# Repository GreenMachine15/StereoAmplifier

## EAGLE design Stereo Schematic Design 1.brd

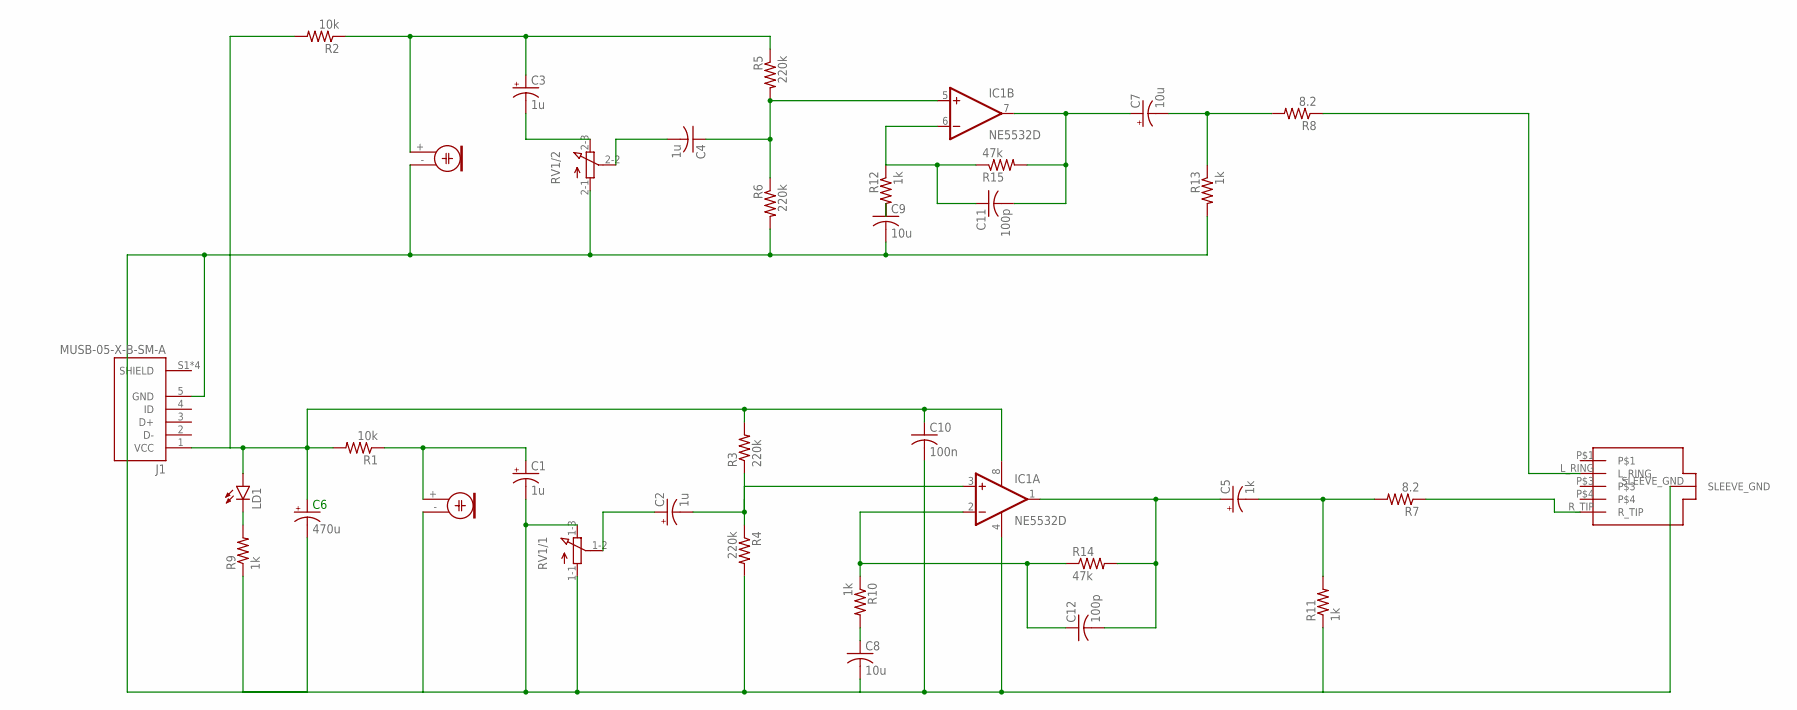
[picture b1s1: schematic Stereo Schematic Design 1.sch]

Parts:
C1, C2, C3: 1u; E3,5-8
C4: 1u; C0603
C5: 1k; E3,5-8
C6: 470u; E3,5-8
C7: 10u; E3,5-8
C8, C9: 10u; C0805
C10: 100n; C1206
C11, C12: 100p; C0603
IC1: NE5532D; SO08
J1: MUSB-05-X-B-SM-A; SAMTEC_MUSB-05-X-B-SM-A
LD1: LED3MM
M1, M2: ELECTRET_MICROPHON-TOM-1545P-R; TOM-1545P-R
R1, R2: 10k; R0805
R3, R4, R5, R6: 220k; R0603
R7, R8: 8.2; R0805
R9, R10, R11, R12: 1k; R1206
R13: 1k; 0204/7
R14, R15: 47k; 0204/7
RV1: 3RP/1610G
U$1: KORTAKJACK; REDPHONEJACK

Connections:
unnamed: C6.+, C10.1, IC1.8 (V+), J1.1 (VCC), LD1.A, R1.2, R2.2, R3.2
unnamed: LD1.K (C), R9.2
unnamed: C1.-, C8.2, C9.2, C10.2, IC1.4 (V-), J1.5 (GND), M2.- (2), R4.2, R6.2, R11.1, R13.2, RV1.1-1 (A), RV1.1-3 (E), RV1.2-1 (A), U$1.SLEEVE_GND
unnamed: C1.+, M1.+ (1), R1.1
unnamed: C8.1, R10.2
unnamed: C2.+, RV1.1-2 (S)
unnamed: C12.1, IC1.2 (-IN), R10.1, R14.1
unnamed: C5.+, C12.2, IC1.1 (OUT), R14.2
unnamed: C6.-, R9.1
unnamed: C2.-, IC1.3 (+IN), R3.1, R4.1
unnamed: C5.-, R7.2, R11.2
unnamed: R7.1, U$1.R_TIP
unnamed: C3.+, M2.+ (1), R2.1, R5.1
unnamed: C3.-, RV1.2-3 (E)
unnamed: C4.2, RV1.2-2 (S)
unnamed: C4.1, IC1.5 (+IN), R5.2, R6.1
unnamed: C11.1, IC1.6 (-IN), R12.1, R15.1
unnamed: C9.1, R12.2
unnamed: C7.+, C11.2, IC1.7 (OUT), R15.2
unnamed: C7.-, R8.2, R13.1
unnamed: R8.1, U$1.L_RING

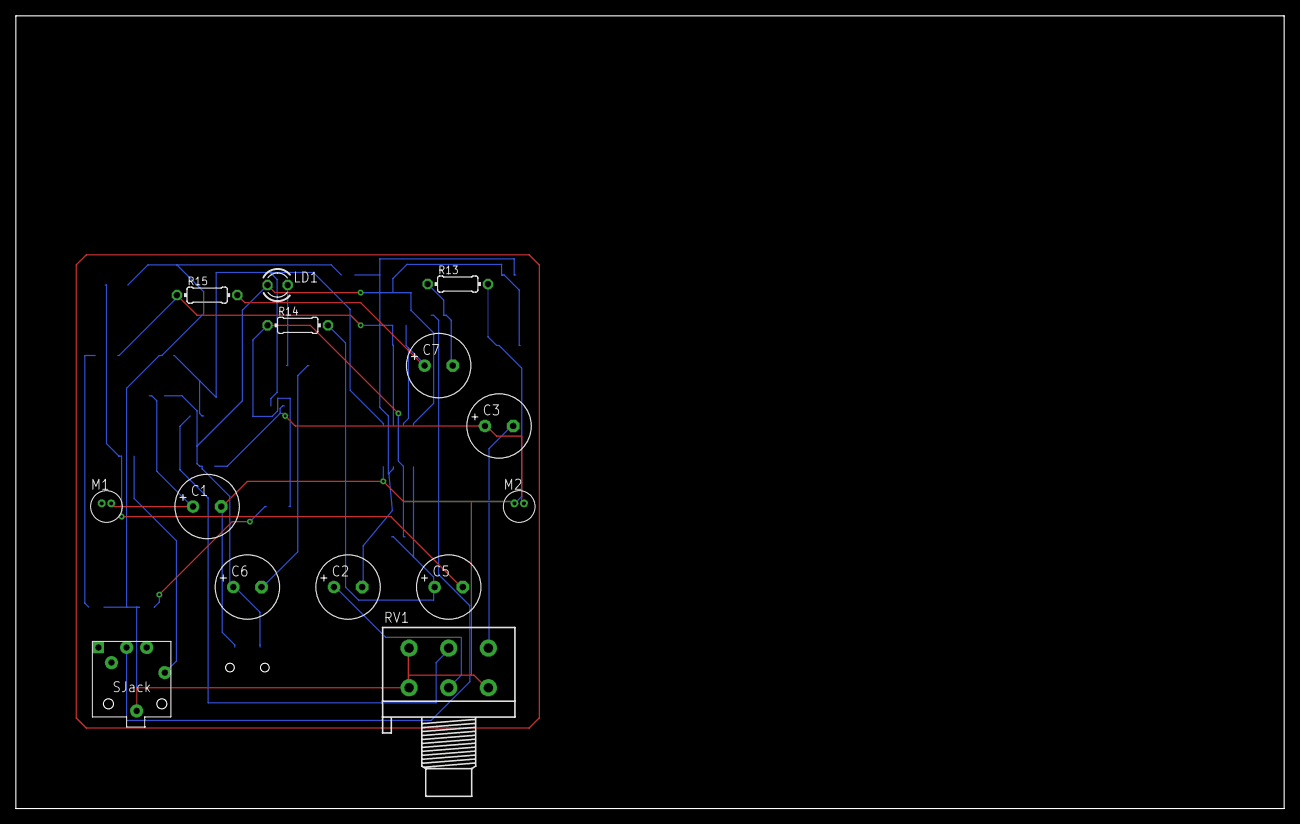
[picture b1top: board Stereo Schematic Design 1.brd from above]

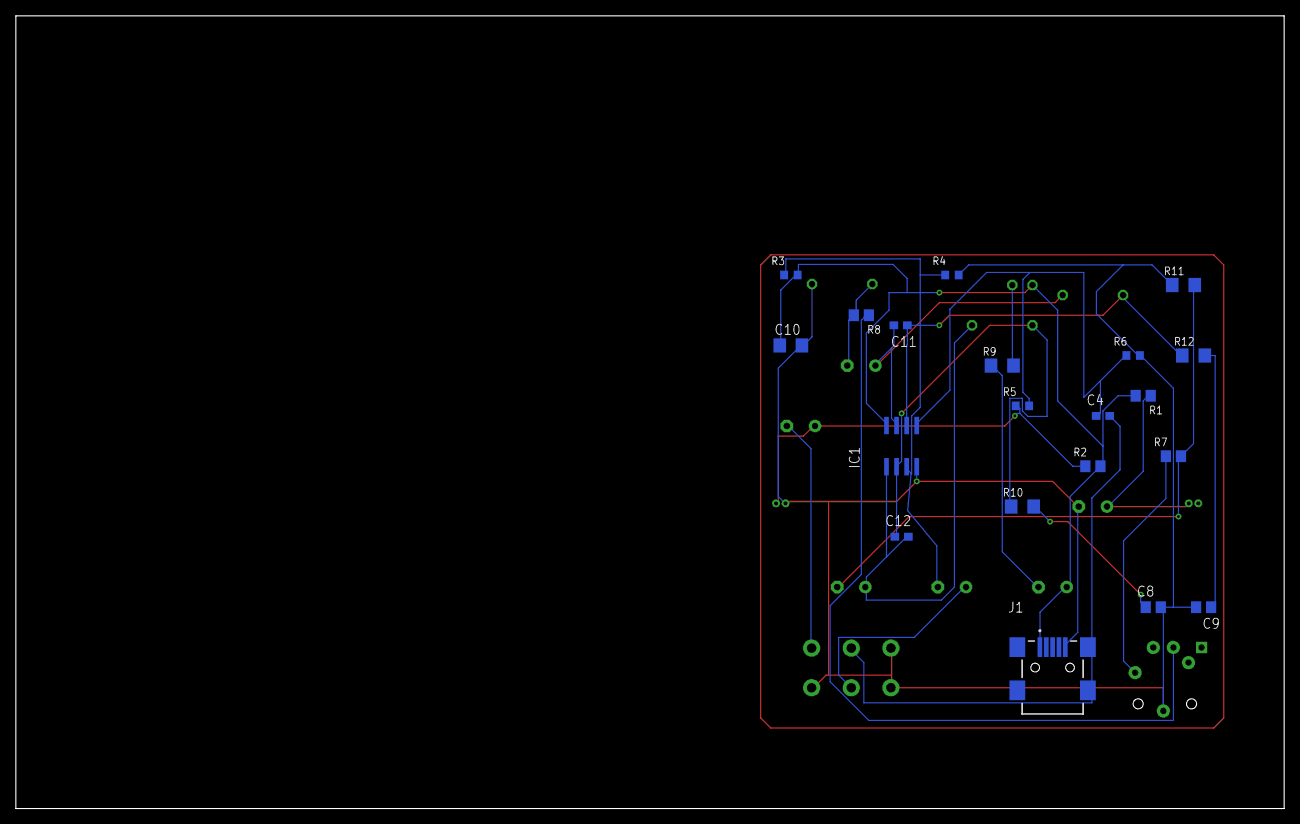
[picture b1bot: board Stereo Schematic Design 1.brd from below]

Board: 2 copper layers, 160.0 x 100.0 mm, 34 parts (20 on the bottom side), 21 nets.
